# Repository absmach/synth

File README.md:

<div align="center">

### Design circuit boards as code.

Turn text-based circuit designs into KiCad schematics, PCB layouts, and bills of materials.

[Install](#install) · [Quick Start](#quick-start) · [Features](#features) · [Examples](#examples) · [Documentation](https://absmach.eu/docs/synth/user-guide/quick-start/) · [Contributing](#contributing)

</div>

## Introduction

Synth is an open-source compiler for electronic circuit boards. Describe components, connections, and board constraints in **SynthSpec**, a text-based design language; Synth checks the design and generates KiCad schematics, PCB layouts, and a bill of materials. Your `.synth` files hold the design intent, so you can edit them in your usual editor and review changes in Git. Engineers drive it from the command line, and AI agents drive the same compiler through its **Model Context Protocol (MCP)** server.

```synth
board "env_logger" {
    layers 2
    manufacturer "jlcpcb"

    group "USB-C INPUT / 3V3 LDO" color "#c2410c" {
      component J1: connector "usb_c_receptacle"
      component U1: regulator "ams1117_3v3" value "AMS1117-3.3"
      component C2: capacitor "c_generic_0805" value "22uF"
    }

    connect J1.vbus -> U1.vin
    connect J1.gnd  -> U1.gnd
    connect U1.vin  -> C2.p1
}
```

_An excerpt from the [environmental logger](examples/env_logger/env_logger.synth); the full design adds the MCU, sensor, CC pull-downs, and decoupling that the checks require._

<div align="center">

_An agent designing a two-layer NE555 LED blinker through the MCP server: searching the registry, authoring a missing part, setting placement overrides, and validating the board._

</div>

## Install

### Prebuilt binary

Every [release](https://github.com/absmach/synth/releases) ships a `synth` binary for five platforms, each with a SHA-256 checksum beside it.

| Platform       | Asset                     |
| -------------- | ------------------------- |
| Linux x86-64   | `synth-linux-amd64`       |
| Linux arm64    | `synth-linux-arm64`       |
| macOS arm64    | `synth-darwin-arm64`      |
| macOS x86-64   | `synth-darwin-amd64`      |
| Windows x86-64 | `synth-windows-amd64.exe` |

```bash
base="https://github.com/absmach/synth/releases/latest/download"
asset="synth-linux-amd64"          # pick your platform from the table above

curl -LO "$base/$asset"
curl -LO "$base/$asset.sha256"
sha256sum -c "$asset.sha256"       # macOS: shasum -a 256 -c "$asset.sha256"

sudo install -m 755 "$asset" /usr/local/bin/synth
synth --version
```

Verify the checksum before running the binary. On Windows, check it with `certutil -hashfile synth-windows-amd64.exe SHA256` and compare against the `.sha256` file.

The Linux binaries are built against glibc 2.35, so they run on Debian Bookworm, Ubuntu 22.04, and newer.

> [!NOTE]
> The component registry and example designs ship inside the repository and track `main`, which has moved ahead of the latest release. Pair a prebuilt binary with its own tag (`git checkout v0.1.1`, where the example paths differ from those below), or install from source to follow the Quick Start as written.

### Cargo

Synth is not on crates.io, so install it from Git. Requires Rust 1.85 or newer.

```bash
# Latest release
cargo install --git https://github.com/absmach/synth --tag v0.1.1 --locked synth-cli

# Current main
cargo install --git https://github.com/absmach/synth --locked synth-cli
```

> [!WARNING]
> Do not run `cargo install synth-cli`. The `synth-cli` crate on crates.io is an unrelated project — a WebAssembly-to-ARM compiler — not this one.

### From source

```bash
git clone https://github.com/absmach/synth.git
cd synth
cargo build -p synth-cli --release
./target/release/synth --help
```

The repository pins its toolchain in `rust-toolchain.toml`, so rustup fetches the right version automatically.

## Quick Start

Validate the minimal example and export a KiCad project. The example designs come from a checkout, so clone the repository (or `cd` into it) first:

```bash
synth validate fixtures/designs/hello.synth
synth export-kicad fixtures/designs/hello.synth --out output/hello
```

The minimal example declares an empty two-layer board. Use the [example designs](#examples) to explore circuits with components and connections.

For machine-readable diagnostics:

```bash
synth validate examples/env_logger/env_logger.synth --format json
```

Open exported projects in KiCad. Optional Gerber, drill, and STEP exports require `kicad-cli`; see the [KiCad workflow guide](docs/kicad-workflows.md) for export and review details.

For CI and release gates, `synth check DESIGN.synth --json` is the deterministic, model-free gate for validation and DRC. A check that could not run is reported as `unknown` and blocks just as a failure does — see [release checks](docs/release-checks.md).

### Logging

Progress, retries, and degraded-check notices go to stderr as structured log events; stdout carries only the command's own output (JSON, reports, listings), so a pipeline can parse it without stripping prefixes. The default level is info. `-v` raises it to debug, `-vv` to trace, and `-q` shows errors only. `SYNTH_LOG` overrides both when one stage needs more detail:

```bash
synth -v export-kicad board.synth --out output/board
SYNTH_LOG=synth_router=debug,synth=info synth route board.synth
```

### Agent Integration

Start the MCP server over standard input and output:

```bash
synth mcp --stdio
```

Agents can retrieve the SynthSpec language reference, search the registry, validate designs, apply fixes, and invoke compiler stages. See the [MCP guide](crates/synth-mcp/README.md) for transports and tool details.

## How It Works

```mermaid
flowchart LR
    source["SynthSpec source"] --> compiler["Parse & resolve"]
    compiler --> checks["Validate"]
    checks --> layout["Place & route"]
    layout --> export["KiCad project & BOM"]
    checks --> feedback["Diagnostics & fixes"]
    feedback --> source
```

Synth resolves parts from a component registry and lowers the source into a typed board representation. Compiler stages use that shared representation for electrical checks, layout, routing, and export. A local browser viewer displays the schematic and diagnostics as you edit.

## Features

| Area               | Capabilities                                                                                                                                    |
| ------------------ | ----------------------------------------------------------------------------------------------------------------------------------------------- |
| Design language    | SynthSpec parser, typed board IR, components, connections, differential pairs, keepouts, and placement hints                                    |
| Validation         | Electrical-rule checks, design-rule checks, structured diagnostics with source locations and suggested fixes, and SMT-backed quantitative fixes |
| Layout and routing | Deterministic schematic layout, component placement, and multilayer routing, so generated artifacts are reproducible                            |
| KiCad integration  | Project, schematic, PCB, and BOM export; optional fabrication outputs through `kicad-cli`                                                       |
| Component registry | Versioned parts, project and user overlays, search, import, and authoring tools                                                                 |
| Developer tools    | CLI, JSON diagnostics, and an MCP server exposing validation, registry search, placement, routing, and export                                   |

## Examples

| Design                                                                                             | What it demonstrates                                                          |
| -------------------------------------------------------------------------------------------------- | ----------------------------------------------------------------------------- |
| [Hello](fixtures/designs/hello.synth)                                                              | The smallest board declaration                                                |
| [Resistor divider](examples/divider/divider.synth)                                                 | A DC operating-point simulation with `synth sim`                              |
| [RC filter](examples/rc_filter/rc_filter.synth)                                                    | An AC sweep measuring the -3 dB corner with `synth sim`                       |
| [LED current](examples/led/led.synth)                                                              | A branch-current measure checked against a limit with `synth sim`             |
| [Environmental logger](examples/env_logger/env_logger.synth)                                       | USB-C power, a regulator, an MCU, an environmental sensor, and a debug header |
| [Sensor logger](examples/sensor_logger/sensor_logger.synth)                                        | A larger design with dual I²C sensors, SPI flash, and status LEDs             |
| [Placement and differential pairs](examples/placement_and_diff_pair/placement_and_diff_pair.synth) | Placement hints, differential-pair constraints, and keepout regions           |
| [RP2350 development board](examples/rp2350/)                                                       | Clean-netlist FreeRouting, zone refill, and compact outlines                  |

Additional language and validation cases live in [fixtures](fixtures/designs/README.md). Part definitions live in the [component registry](registry/README.md).

_Pre-generated compact RP2350 routed review artifact; open the [KiCad board](examples/rp2350/rp2350_devboard_freerouting_clean.kicad_pcb)
for an interactive review._

## Documentation

- [Release checks](docs/release-checks.md) — the `synth check` gate, tri-state native stages, and export overrides.
- [KiCad workflows](docs/kicad-workflows.md) — exported projects, validation, BOMs, and fabrication outputs.
- [SPICE simulation](docs/spice-sim.md) — `synth sim` testbenches, analyses, measures and ngspice setup.
- [Schematic procedures](docs/schematic-procedures.md) — schematic generation and review.
- [Diagnostic reference](docs/diagnostics/README.md) — diagnostic codes and repair guidance.
- [Diagnostic protocol](docs/protocol-v1.0.md) — the machine-readable diagnostic format.
- [Component registry](registry/README.md) — part definitions and registry structure.
- [MCP server](crates/synth-mcp/README.md) — agent tools and integration.

## Contributing

Contributions to the compiler, component registry, examples, and documentation are welcome. Use [issues](https://github.com/absmach/synth/issues) to report bugs or discuss a change, and submit a pull request with a focused description and relevant validation.

Before submitting code, run the workspace checks:

```bash
make verify
```

This checks formatting, compilation, Clippy lints, the workspace tests, and registry tests. Run `make help` to see individual development commands.

## License

Synth is licensed under the [Apache License 2.0](LICENSE).

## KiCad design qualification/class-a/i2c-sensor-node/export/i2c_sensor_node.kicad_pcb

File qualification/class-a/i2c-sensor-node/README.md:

# I²C sensor node

A field sensor node: JST-fed 5 V into a 3V3 LDO, an STM32G030 reading two I²C
devices — an environmental sensor and a config EEPROM — with a 4-pin JST
break-out for the host UART. One bus, one set of pull-ups.

Design rationale is in the source comments next to the circuits it explains;
this file is the specification.

## Board

| | |
| --- | --- |
| Size | 78.85 × 43.50 mm |
| Layers | 2 |
| Process | JLCPCB standard (0.127 mm track/clearance, 0.3 mm drill, 0.13 mm ring) |
| Components | 19 |
| Nets | 10 |
| Source | `i2c_sensor_node.synth` |

## Supply

| Rail | Source | Protection |
| --- | --- | --- |
| 5 V in | J1, 2-pin JST PH | F1 500 mA polyfuse, then D1 SS14 series Schottky |
| 3V3 | U1 AMS1117-3.3 | 10 µF in, 1 µF out |

Polyfuse before the Schottky: resettable over-current first, then
reverse-polarity, so a reversed supply meets a blocking diode and a fault
current meets a part that resets rather than one that burns.

## Connectors

| Ref | Part | Carries |
| --- | --- | --- |
| J1 | 2-pin JST PH | 5 V, GND |
| J2 | 4-pin JST PH | host UART, with D2 and D3 clamping both lines |

## I²C bus

One bus, 4.7 kΩ pull-ups on both lines, two devices: a BME680 environmental
sensor and a 24LC256 EEPROM. Each carries its own 100 nF, hinted to sit beside
the part rather than wherever the placer would otherwise put it.

## Measured

One local run of the export and the external router.

| | |
| --- | --- |
| Nets closed | **10 of 10** |
| Open | **0** |
| Routed copper | 408.9 mm over 155 segments and 15 vias |
| Tracks below the 0.127 mm floor | **0** |
| Vias below the 0.3 mm drill or 0.13 mm ring | **0** |
| `kicad-cli pcb drc` | 9 errors, 0 unconnected items, 10 warnings |

Three consecutive exports produce a byte-identical schematic and BOM.

### DRC detail

| Severity | Finding | Count |
| --- | --- | --- |
| error | clearance | 7 |
| error | via diameter | 2 |
| warning | silkscreen over copper | 6 |
| warning | library footprint mismatch | 3 |
| warning | dangling via | 1 |

Every net on this board closes and no copper is below the fabrication floor.
What remains is seven places where the router worked inside the clearance the
board asked for.

## Limitations

- **Seven clearance violations.** The board routes completely but not to its
  own declared clearance in seven places; each is copper a human would nudge.
- **One via lands inside a pad** and via-in-pad is not declared, so the
  package is refused. On a two-layer board at this pitch that via is avoidable
  by hand.
- Six silkscreen-over-copper warnings are reference designators crossing pads.
  They are cosmetic on a fabricated board and would be fixed in a silkscreen
  pass that Synth does not perform.
- No fabrication artifacts are produced; the package is refused as
  `UNTRUSTED / NOT FOR FABRICATION`.
- No part carries distributor identity, so the BOM is not orderable as it
  stands.

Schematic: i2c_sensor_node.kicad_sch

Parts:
C1, C2, C4: 10uF; C_0805_2012Metric
C3: 47uF; CP_EIA-3528-21_Kemet-B
C5, C6, C8, C10, C11, C12: 100nF; C_0603_1608Metric
C7: 4.7uF; C_0603_1608Metric
D1, D14: 1N5819; D_SOD-123; MPN 1N5819HW-7-F; LCSC C82544
D4: PTVS6V0S1UR; Nexperia_CFP3_SOD-123W; MPN PTVS6V0S1UR
D7, D8, D9, D10, D11, D12, D13, D19, D20, D21, D22, D23, D24: 3.3V zener; D_SOD-123
D15: GREEN; LED_0603_1608Metric; MPN LTST-C190KGKT
F1: 0.5A hold; Fuse_1812_4532Metric
H2, H3: (no value); MountingHole_2.5mm
J1: JST S2B-XH-A-1; JST_XH_S2B-XH-A-1_1x02_P2.50mm_Horizontal
J3: JST S4B-PH-K-S; JST_PH_S4B-PH-K_1x04_P2.00mm_Horizontal
J4: SWD; PinHeader_1x05_P2.54mm_Vertical
J5: GPIO; PinHeader_1x12_P2.54mm_Vertical
R3: 10k; R_0603_1608Metric
R9, R10: 4.7k; R_0603_1608Metric
R11, R15, R16, R17, R18, R19, R20, R21, R22: 330; R_0603_1608Metric
R12: 1k; R_0603_1608Metric
R13, R14: 100; R_0603_1608Metric
R23: 100; R_0805_2012Metric
R24: 680; R_0603_1608Metric
SW1: RESET; SW_SPST_PTS645Sx43SMTR92
U1: AMS1117-3.3; SOT-223-3_TabPin2; MPN AMS1117-3.3; LCSC C6186
U2: STM32G030F6P6; TSSOP-20_4.4x6.5mm_P0.65mm; MPN STM32G030F6P6
U3: BME680; Bosch_LGA-8_3x3mm_P0.8mm_ClockwisePinNumbering; MPN BME680
U5: 24LC256-I/SN; SOIC-8_3.9x4.9mm_P1.27mm; MPN 24LC256-I/SN; LCSC C411625

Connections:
3V3_REF: J3.4, J4.1, J5.1, R23.2
+3V3: C3.1, C4.1, C5.1, C6.1, C7.1, C10.1, C11.1, C12.1, D14.2 (A), R3.1, R9.1, R10.1, R24.1, U1.2 (VO), U2.4 (VDD), U3.2 (CSB), U3.6 (VDDIO), U3.8 (VDD), U5.8 (VCC)
+5V_PROT: C1.1, C2.1, D1.1 (K), D4.1 (K), U1.3 (VI)
GND: C1.2, C2.2, C3.2, C4.2, C5.2, C6.2, C7.2, C8.2, C10.2, C11.2, C12.2, D4.2 (A), D7.2 (A), D8.2 (A), D9.2 (A), D10.2 (A), D11.2 (A), D12.2 (A), D13.2 (A), D15.1 (K), D19.2 (A), D20.2 (A), D21.2 (A), D22.2 (A), D23.2 (A), D24.2 (A), J1.2, J3.1, J4.4, J5.2, J5.6, J5.10, SW1.2, U1.1 (GND), U2.5 (VSS), U3.1 (GND), U3.5 (SDO), U3.7 (GND), U5.1 (A0), U5.2 (A1), U5.3 (A2), U5.4 (GND), U5.7 (WP)
GPIO_PA0: J5.3, R15.2
GPIO_PA0_MCU: D10.1 (K), R15.1, U2.7 (PA0)
GPIO_PA1: J5.4, R16.2
GPIO_PA1_MCU: D20.1 (K), R16.1, U2.8 (PA1)
GPIO_PA4: J5.5, R17.2
GPIO_PA4_MCU: D11.1 (K), R17.1, U2.11 (PA4)
GPIO_PA5: J5.7, R18.2
GPIO_PA5_MCU: D21.1 (K), R18.1, U2.12 (PA5)
GPIO_PA6: J5.8, R19.2
GPIO_PA6_MCU: D12.1 (K), R19.1, U2.13 (PA6)
GPIO_PA7: J5.9, R20.2
GPIO_PA7_MCU: D22.1 (K), R20.1, U2.14 (PA7)
GPIO_PB0: J5.11, R21.2
GPIO_PB0_MCU: D13.1 (K), R21.1, U2.15 (PA8/PB0/PB1/PB2)
GPIO_PB9: J5.12, R22.2
GPIO_PB9_MCU: D23.1 (K), R22.1, U2.2 (PB9/PC14)
I2C_SCL: R10.2, U2.20 (PB3/PB4/PB5/PB6), U3.4 (SCK), U5.6 (SCL)
I2C_SDA: R9.2, U2.1 (PB7/PB8), U3.3 (SDI), U5.5 (SDA)
LED_PWR: D15.2 (A), R24.2
NRST: C8.1, D19.1 (K), J4.5, R3.2, SW1.1, U2.6 (NRST)
REF_D: D14.1 (K), R23.1
SWCLK: D9.1 (K), J4.3, R14.2
SWCLK_MCU: R14.1, U2.19 (PA14/PA15)
SWDIO: D8.1 (K), J4.2, R13.2
SWDIO_MCU: R13.1, U2.18 (PA13)
U2_RX: D24.1 (K), R12.1, U2.10 (PA3)
U2_TX: D7.1 (K), R11.1, U2.9 (PA2)
UART_RX: J3.3, R12.2
UART_TX: J3.2, R11.2
VIN_5V_FUSED: D1.2 (A), F1.2
VIN_5V_RAW: F1.1, J1.1

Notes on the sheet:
5V INPUT: FUSE THEN DIODE
3V3 REGULATOR
STM32G030 MCU
I2C SENSING
UART BREAKOUT
GPIO HEADER
MOUNTING
J1 pin 1 = +5 V, pin 2 = GND (JST XHP-2). Fuse first, then the
reverse-polarity diode D1.
D4 clamps transients on +5V_PROT, behind D1 so a reversed supply never
forward-biases it.
AMS1117 tab is VOUT. Load budget 100 mA: P = (5.0 - 3.3) x 0.1 A =
0.17 W, thetaJA 90 C/W gives a 15 C rise (125 C limit).
LED (VF 1.9 to 2.4 V): 1.3 to 2.1 mA through 680 R. C3 is 47 uF
tantalum (22 uF required).
J4: 1 = 3V3_REF, 2 = SWDIO, 3 = SWCLK, 4 = GND, 5 = NRST. PA14 is
SWCLK and BOOT0.
D8, D9, D19 are 3.3 V zeners; a 5 V fault through 100 R is (5 - 3.3) /
100 = 17 mA, 56 mW.
BME680 SDO low = 0x76, CSB high = I2C. 24LC256 A2:A0 low = 0x50. No
collision.
One pull-up pair, 4.7k each, for the whole bus.
J3: 1 GND, 2 UART_TX, 3 UART_RX, 4 3V3_REF (3 mA max). Host logic 3.3
V to 5 V.
D7, D24 are 3.3 V zeners behind 330 R and 1 k: a 5 V fault is 5.2 mA
(17 mW) and 1.7 mA (5.6 mW).
J5: 1 3V3_REF, 2 GND, 3 PA0, 4 PA1, 5 PA4, 6 GND, 7 PA5, 8 PA6, 9 PA7,
10 GND, 11 PB0, 12 PB9.
D10..D13, D20..D23: one 3.3 V zener per line behind 330 R; a 5 V fault
is 5.2 mA, 17 mW. 3V3_REF is +3V3 through D14 and 100 R, 3 mA max.
H2, H3: two M2.5 non-plated mounting holes at opposite (diagonal)
corners.

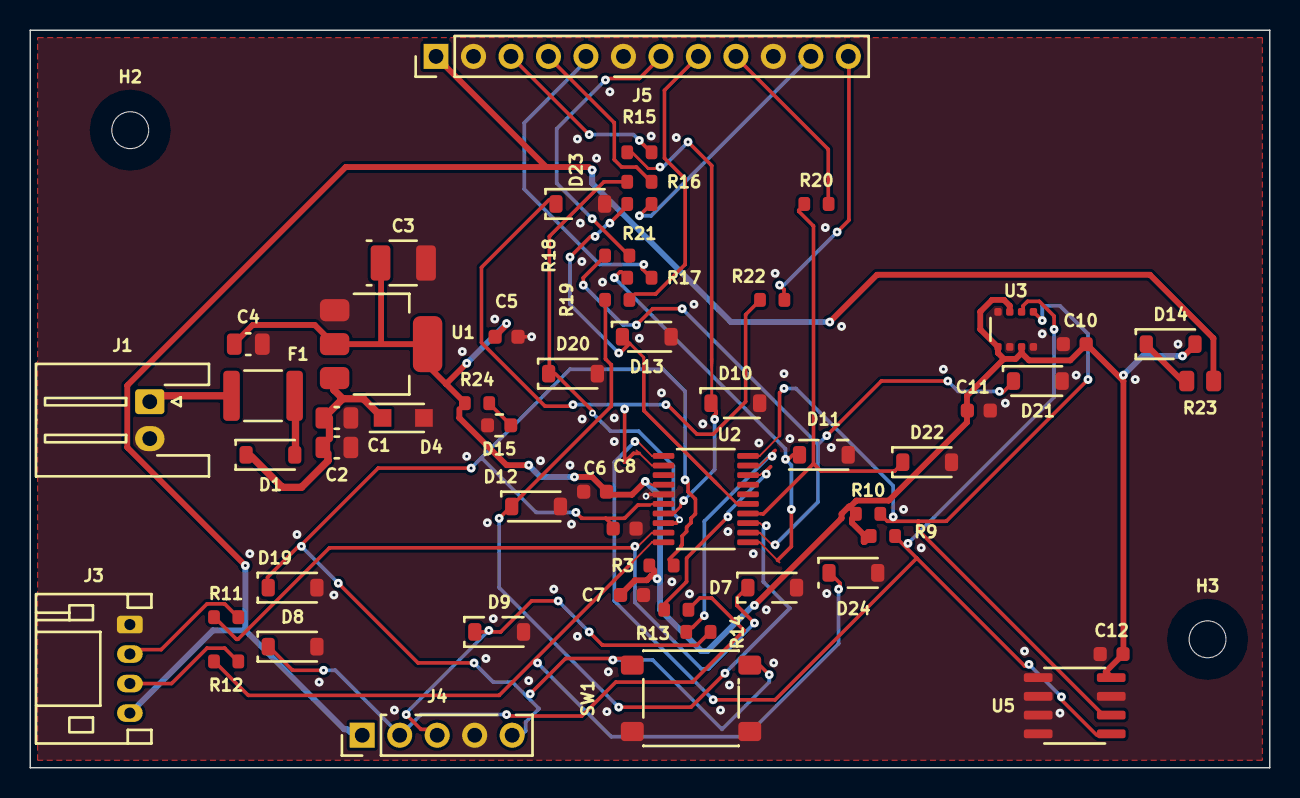
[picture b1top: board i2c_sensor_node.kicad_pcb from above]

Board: 2 copper layers, 84.0 x 50.0 mm, 57 parts (0 on the bottom side), 35 nets.

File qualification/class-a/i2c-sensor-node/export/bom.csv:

refdes,value,kind,description,kicad_symbol,kicad_footprint,lcsc_pn,mpn
C1,10uF,capacitor,"Generic 0805 MLCC, X7R/X5R, any value",Device:C,Capacitor_SMD:C_0805_2012Metric,,
C10,100nF,capacitor,"Generic 0603 MLCC, X7R/X5R, any value",Device:C,Capacitor_SMD:C_0603_1608Metric,,
C11,100nF,capacitor,"Generic 0603 MLCC, X7R/X5R, any value",Device:C,Capacitor_SMD:C_0603_1608Metric,,
C12,100nF,capacitor,"Generic 0603 MLCC, X7R/X5R, any value",Device:C,Capacitor_SMD:C_0603_1608Metric,,
C2,10uF,capacitor,"Generic 0805 MLCC, X7R/X5R, any value",Device:C,Capacitor_SMD:C_0805_2012Metric,,
C3,47uF,capacitor,"47µF 16V tantalum capacitor, polarised, 3528 case",Device:C_Polarized,Capacitor_Tantalum_SMD:CP_EIA-3528-21_Kemet-B,,
C4,10uF,capacitor,"Generic 0805 MLCC, X7R/X5R, any value",Device:C,Capacitor_SMD:C_0805_2012Metric,,
C5,100nF,capacitor,"Generic 0603 MLCC, X7R/X5R, any value",Device:C,Capacitor_SMD:C_0603_1608Metric,,
C6,100nF,capacitor,"Generic 0603 MLCC, X7R/X5R, any value",Device:C,Capacitor_SMD:C_0603_1608Metric,,
C7,4.7uF,capacitor,"Generic 0603 MLCC, X7R/X5R, any value",Device:C,Capacitor_SMD:C_0603_1608Metric,,
C8,100nF,capacitor,"Generic 0603 MLCC, X7R/X5R, any value",Device:C,Capacitor_SMD:C_0603_1608Metric,,
D1,1N5819,diode,"Diodes Inc. 1N5819HW-7-F, 40 V 1 A Schottky diode, SOD-123, low forward voltage",Device:D_Schottky,Diode_SMD:D_SOD-123,C82544,1N5819HW-7-F
D10,3.3V zener,diode,"3.3V Zener diode, SOD-123",Device:D_Zener,Diode_SMD:D_SOD-123,,
D11,3.3V zener,diode,"3.3V Zener diode, SOD-123",Device:D_Zener,Diode_SMD:D_SOD-123,,
D12,3.3V zener,diode,"3.3V Zener diode, SOD-123",Device:D_Zener,Diode_SMD:D_SOD-123,,
D13,3.3V zener,diode,"3.3V Zener diode, SOD-123",Device:D_Zener,Diode_SMD:D_SOD-123,,
D14,1N5819,diode,"Diodes Inc. 1N5819HW-7-F, 40 V 1 A Schottky diode, SOD-123, low forward voltage",Device:D_Schottky,Diode_SMD:D_SOD-123,C82544,1N5819HW-7-F
D15,GREEN,diode,"Lite-On LTST-C190KGKT green AlInGaP LED, 0603, Vf 1.9 to 2.4V at 20mA",Device:LED,LED_SMD:LED_0603_1608Metric,,LTST-C190KGKT
D19,3.3V zener,diode,"3.3V Zener diode, SOD-123",Device:D_Zener,Diode_SMD:D_SOD-123,,
D20,3.3V zener,diode,"3.3V Zener diode, SOD-123",Device:D_Zener,Diode_SMD:D_SOD-123,,
D21,3.3V zener,diode,"3.3V Zener diode, SOD-123",Device:D_Zener,Diode_SMD:D_SOD-123,,
D22,3.3V zener,diode,"3.3V Zener diode, SOD-123",Device:D_Zener,Diode_SMD:D_SOD-123,,
D23,3.3V zener,diode,"3.3V Zener diode, SOD-123",Device:D_Zener,Diode_SMD:D_SOD-123,,
D24,3.3V zener,diode,"3.3V Zener diode, SOD-123",Device:D_Zener,Diode_SMD:D_SOD-123,,
D4,PTVS6V0S1UR,diode,"Nexperia PTVS6V0S1UR 400 W unidirectional TVS, 6.0 V standoff, SOD123W, for VBUS and CC",Device:D_Zener,Diode_SMD:Nexperia_CFP3_SOD-123W,,PTVS6V0S1UR
D7,3.3V zener,diode,"3.3V Zener diode, SOD-123",Device:D_Zener,Diode_SMD:D_SOD-123,,
D8,3.3V zener,diode,"3.3V Zener diode, SOD-123",Device:D_Zener,Diode_SMD:D_SOD-123,,
D9,3.3V zener,diode,"3.3V Zener diode, SOD-123",Device:D_Zener,Diode_SMD:D_SOD-123,,
F1,0.5A hold,fuse,"Resettable polyfuse (PPTC), 0.5 A hold, 2-pin, 1812. Generic: MPN needs sourcing.",Device:Polyfuse,Fuse:Fuse_1812_4532Metric,,
H2,(no value),mounting_hole,M2.5 non-plated mounting hole (NPTH) for a board corner,Mechanical:MountingHole,MountingHole:MountingHole_2.5mm,,
H3,(no value),mounting_hole,M2.5 non-plated mounting hole (NPTH) for a board corner,Mechanical:MountingHole,MountingHole:MountingHole_2.5mm,,
J1,JST S2B-XH-A-1,connector,"JST XH-series 2-pin wire-to-board connector, 2.0mm pitch",Connector_Generic:Conn_01x02,Connector_JST:JST_XH_S2B-XH-A-1_1x02_P2.50mm_Horizontal,,
J3,JST S4B-PH-K-S,connector,"JST PH-series 4-pin wire-to-board connector, 2.0mm pitch",Connector_Generic:Conn_01x04,Connector_JST:JST_PH_S4B-PH-K_1x04_P2.00mm_Horizontal,,
J4,SWD,connector,"1x5 through-hole pin header, 2.54 mm pitch (SWD); datasheet_url is the product page of the Harwin M20 series, no manufacturer PDF link was verifiable",Connector_Generic:Conn_01x05,Connector_PinHeader_2.54mm:PinHeader_1x05_P2.54mm_Vertical,,
J5,GPIO,connector,"1x12 through-hole pin header, 2.54 mm pitch (GPIO); datasheet_url is the product page of the Harwin M20 series, no manufacturer PDF link was verifiable",Connector_Generic:Conn_01x12,Connector_PinHeader_2.54mm:PinHeader_1x12_P2.54mm_Vertical,,
R10,4.7k,resistor,"Generic 0603 thick-film resistor, any value",Device:R_US,Resistor_SMD:R_0603_1608Metric,,
R11,330,resistor,"Generic 0603 thick-film resistor, any value",Device:R_US,Resistor_SMD:R_0603_1608Metric,,
R12,1k,resistor,"Generic 0603 thick-film resistor, any value",Device:R_US,Resistor_SMD:R_0603_1608Metric,,
R13,100,resistor,"Generic 0603 thick-film resistor, any value",Device:R_US,Resistor_SMD:R_0603_1608Metric,,
R14,100,resistor,"Generic 0603 thick-film resistor, any value",Device:R_US,Resistor_SMD:R_0603_1608Metric,,
R15,330,resistor,"Generic 0603 thick-film resistor, any value",Device:R_US,Resistor_SMD:R_0603_1608Metric,,
R16,330,resistor,"Generic 0603 thick-film resistor, any value",Device:R_US,Resistor_SMD:R_0603_1608Metric,,
R17,330,resistor,"Generic 0603 thick-film resistor, any value",Device:R_US,Resistor_SMD:R_0603_1608Metric,,
R18,330,resistor,"Generic 0603 thick-film resistor, any value",Device:R_US,Resistor_SMD:R_0603_1608Metric,,
R19,330,resistor,"Generic 0603 thick-film resistor, any value",Device:R_US,Resistor_SMD:R_0603_1608Metric,,
R20,330,resistor,"Generic 0603 thick-film resistor, any value",Device:R_US,Resistor_SMD:R_0603_1608Metric,,
R21,330,resistor,"Generic 0603 thick-film resistor, any value",Device:R_US,Resistor_SMD:R_0603_1608Metric,,
R22,330,resistor,"Generic 0603 thick-film resistor, any value",Device:R_US,Resistor_SMD:R_0603_1608Metric,,
R23,100,resistor,"Generic 0805 thick-film resistor, any value",Device:R_US,Resistor_SMD:R_0805_2012Metric,,
R24,680,resistor,"Generic 0603 thick-film resistor, any value",Device:R_US,Resistor_SMD:R_0603_1608Metric,,
R3,10k,resistor,"Generic 0603 thick-film resistor, any value",Device:R_US,Resistor_SMD:R_0603_1608Metric,,
R9,4.7k,resistor,"Generic 0603 thick-film resistor, any value",Device:R_US,Resistor_SMD:R_0603_1608Metric,,
SW1,RESET,switch,Generic SPST tactile button,Switch:SW_Push,Button_Switch_SMD:SW_SPST_PTS645Sx43SMTR92,,
U1,AMS1117-3.3,regulator,"AMS1117-3.3 fixed 3.3V LDO regulator, SOT-223 — common JLC stock",Regulator_Linear:AMS1117-3.3,Package_TO_SOT_SMD:SOT-223-3_TabPin2,C6186,AMS1117-3.3
U2,STM32G030F6P6,mcu,"STMicro STM32G030F6P6 Cortex-M0+ 64 MHz, 32 KB flash, 8 KB RAM, TSSOP-20. Pin map checked against KiCad MCU_ST_STM32G0:STM32G030F6Px",MCU_ST_STM32G0:STM32G030F6Px,Package_SO:TSSOP-20_4.4x6.5mm_P0.65mm,,STM32G030F6P6
U3,BME680,sensor,"Bosch BME680 T/RH/P/gas sensor, 3.0x3.0 mm 8-pin LGA, I2C/SPI. Pins checked against KiCad Sensor:BME680; footprint is the 3x3 mm 0.8 mm pitch one whose KiCad description cites the BME680 datasheet",Sensor:BME680,Package_LGA:Bosch_LGA-8_3x3mm_P0.8mm_ClockwisePinNumbering,,BME680
U5,24LC256-I/SN,memory,"Microchip 24LC256-I/SN 256 Kbit I2C EEPROM, SOIC-8. Pin map checked against KiCad Memory_EEPROM:24LC256",Memory_EEPROM:24LC256,Package_SO:SOIC-8_3.9x4.9mm_P1.27mm,C411625,24LC256-I/SN

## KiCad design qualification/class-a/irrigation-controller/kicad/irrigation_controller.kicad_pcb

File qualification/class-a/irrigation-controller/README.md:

# Irrigation controller (Class A, case 1)

A two-zone irrigation controller powered from 12 V DC: an input fuse, a TVS and an ideal-diode reverse-polarity stage, an MP2307 buck to 3.3 V, an STM32G030 microcontroller, two low-side solenoid drivers, two switched resistive soil probes, a flow-pulse input, an I2C header with an ambient light sensor and an EEPROM, an SWD header, and rail decoupling, bleeders, snubbers, indicator LEDs and test points. Two copper layers, JLCPCB process, 79.2 x 70.7 mm, 127 placed items (107 parts and 20 mounting holes and test points). There is no humidity sensor on the board: a breakout attaches to the I2C header at address 0x44.

## The board

| Group | Parts |
|---|---|
| Power input | `J1` JST XH 2-pin supply connector; `F1` Littelfuse 1812L150/16DR resettable fuse (1.5 A hold); `D_TVS` SMAJ13A (13.0 V standoff, 21.5 V clamp at 18.6 A); the ideal-diode stage `U_IDEAL` Texas Instruments LM74700-Q1 (SOT-23-6) driving `Q1` Diodes DMT6007LFG (60 V, 8.5 mOhm maximum at 4.5 V gate drive) with `C_VCAP` and `C_VIN` (100 nF each) at the controller and `C_BULK` (100 uF) on the output; test points `TP_VIN`, `TP_12V` |
| 3.3 V buck | `U1` MPS MP2307DN, input capacitors `C_IN1` and `C_IN2` (10 uF), inductor `L1` Bourns SRN6045TA-100M (10 uH), output capacitors `C_OUT1` and `C_OUT2` (22 uF), feedback divider `R_FBT` 26.1 k and `R_FBB` 10 k, compensation `R_COMP` 5.6 k and `C_COMP` 4.7 nF, soft-start `C_SS`, enable divider `R_EN`; test points `TP_3V3`, `TP_GND` |
| MCU | `U2` STMicroelectronics STM32G030K8T6 (LQFP-32), crystal `Y1` JYJE 3TJ480000FYLBC (8 MHz) with `C_X1` and `C_X2` (6.2 pF), supply capacitors `C_VDD1` and `C_VDD2`, reset network `R_NRST`, `C_NRST` and the tactile switch `SW_RESET`, the 5-pin SWD header `J_SWD`; test points `TP_NRST`, `TP_SWDIO`, `TP_SWCLK` |
| Valves 1 and 2 | per valve: a JST XH 2-pin connector (`J_VALVE1`, `J_VALVE2`), a low-side AO3400A N-MOSFET (`Q_V1`, `Q_V2`) with a 100 ohm gate resistor and a 100 k pull-down, a 1N5819HW flyback diode (`D_FLY1`, `D_FLY2`) and an RC snubber (100 ohm, 10 nF) |
| Soil probes 1 and 2 | per probe: a JST PH 3-pin connector (`J_SOIL1`, `J_SOIL2`), a Si2301CDS P-MOSFET that switches the excitation (`Q_E1`, `Q_E2`), the sense divider and a 10 nF filter |
| Flow input | `J_FLOW` JST PH 3-pin, pull-up `R_FPU`, series resistor `R_FS` and a 3.3 V zener `D_FZ` that clamps the pulse input, filter `C_FL` |
| I2C | `J_I2C` JST PH 4-pin, 4.7 k pull-ups `R_SDA` and `R_SCL`, `U4` Broadcom APDS-9301 ambient light sensor, `U5` Microchip 24LC256 EEPROM, each with a 100 nF capacitor |
| Indicators | `D_PWR` and `D_N2` green (Lite-On LTST-C190KGKT), `D_VALVE` and `D_N1` amber (KENTO KT-0603Y), each with a series resistor |
| Rail decoupling and bleeders | the `+3V3` decoupling group (22 parts: capacitors from 100 nF to 10 uF and the bleeders `R_N1` and `R_N2`) and the 12 V decoupling group (7 parts, with the bleeder `R_B1`) |
| Mechanical | four M2.5 mounting holes, one in each corner; test points on the nets listed above |

The qualification verdict, measurements, evidence and sign-off are in [`QUALIFICATION.md`](QUALIFICATION.md); how the board was made is in [`PROVENANCE.md`](PROVENANCE.md). Gerber content hash `a26463bd09`.

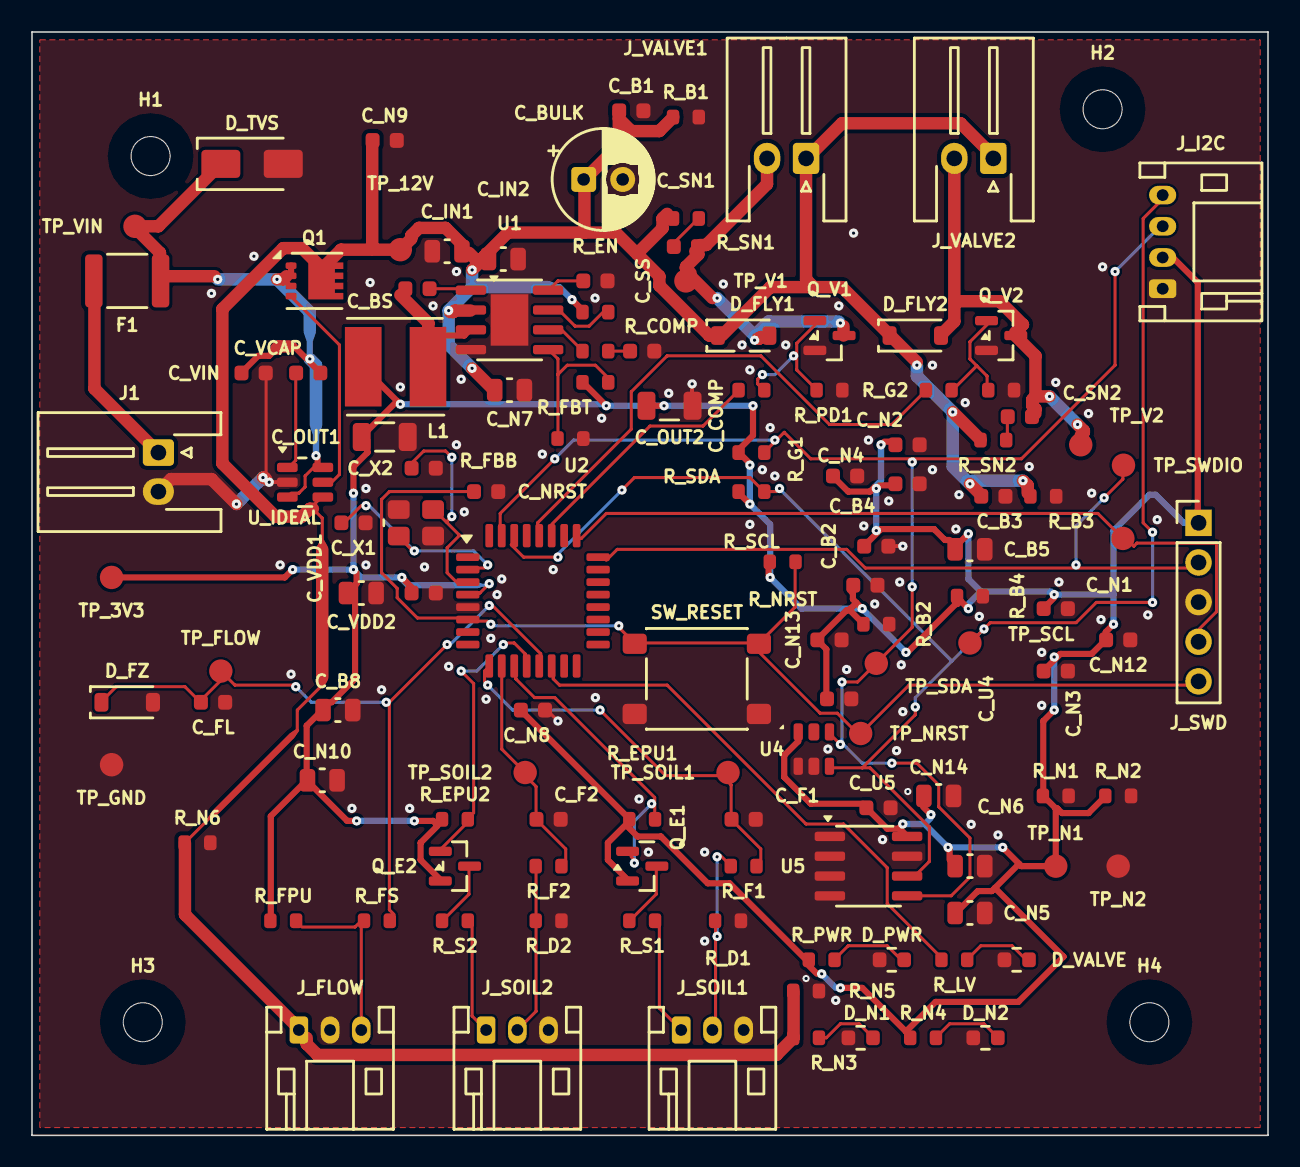
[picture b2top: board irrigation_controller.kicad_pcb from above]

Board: 2 copper layers, 79.2 x 70.7 mm, 127 parts (0 on the bottom side), 46 nets.

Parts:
C_B1, C_B2, C_B3, C_B4: 100nF; C_0603_1608Metric
C_B5, C_B8: 4.7uF; C_0805_2012Metric
C_BS: 10nF; C_0603_1608Metric
C_BULK: 100uF 25V; CP_Radial_D6.3mm_P2.50mm
C_COMP: 4.7nF; C_0603_1608Metric
C_F1, C_F2: 10nF; C_0603_1608Metric
C_FL: 10nF; C_0603_1608Metric
C_IN1, C_IN2: 10uF 25V; C_0805_2012Metric
C_N1, C_N2, C_N3, C_N4, C_N8, C_N9, C_N11, C_N12, C_N13: 100nF; C_0603_1608Metric
C_N5: 10uF; C_0805_2012Metric
C_N6, C_N10, C_N14: 4.7uF; C_0805_2012Metric
C_N7: 10uF 25V; C_0805_2012Metric
C_NRST: 100nF; C_0603_1608Metric
C_OUT1, C_OUT2: 22uF 10V; C_1206_3216Metric
C_SN1, C_SN2: 10nF; C_0603_1608Metric
C_SS: 100nF; C_0603_1608Metric
C_U4, C_U5: 100nF; C_0603_1608Metric
C_VCAP: 100nF; C_0603_1608Metric
C_VDD1: 100nF; C_0603_1608Metric
C_VDD2: 4.7uF; C_0805_2012Metric
C_VIN: 100nF; C_0603_1608Metric
C_X1, C_X2: 6.2pF; C_0603_1608Metric
D_FLY1, D_FLY2: 1N5819HW-7-F; D_SOD-123
D_FZ: (no value); D_SOD-123
D_N1: (no value); LED_0603_1608Metric
D_N2: LTST-C190KGKT; LED_0603_1608Metric
D_PWR: LTST-C190KGKT; LED_0603_1608Metric
D_TVS: SMAJ13A; D_SMA
D_VALVE: (no value); LED_0603_1608Metric
F1: 1812L150/16DR; Fuse_1812_4532Metric
H1, H2, H3, H4: (no value); MountingHole_2.5mm
J1: S2B-XH-A-1(LF)(SN); JST_XH_S2B-XH-A-1_1x02_P2.50mm_Horizontal
J_FLOW: S3B-PH-K-S(LF)(SN); JST_PH_S3B-PH-K_1x03_P2.00mm_Horizontal
J_I2C: S4B-PH-K-S(LF)(SN); JST_PH_S4B-PH-K_1x04_P2.00mm_Horizontal
J_SOIL1, J_SOIL2: S3B-PH-K-S(LF)(SN); JST_PH_S3B-PH-K_1x03_P2.00mm_Horizontal
J_SWD: (no value); PinHeader_1x05_P2.54mm_Vertical
J_VALVE1, J_VALVE2: S2B-XH-A-1(LF)(SN); JST_XH_S2B-XH-A-1_1x02_P2.50mm_Horizontal
L1: SRN6045TA-100M; L_Bourns_SRN6045TA
Q1: DMT6007LFG-7; Diodes_PowerDI3333-8
Q_E1, Q_E2: SI2301CDS-T1-GE3; SOT-23
Q_V1, Q_V2: AO3400A; SOT-23
R_B1, R_B2: 100k; R_0603_1608Metric
R_B3, R_B4: 47k; R_0603_1608Metric
R_COMP: 5.6k; R_0603_1608Metric
R_D1, R_D2: 10k; R_0603_1608Metric
R_EN: 100k; R_0603_1608Metric
R_EPU1, R_EPU2: 100k; R_0603_1608Metric
R_F1, R_F2: 1k; R_0603_1608Metric
R_FBB: 10k; R_0603_1608Metric
R_FBT: 26.1k; R_0603_1608Metric
R_FPU: 10k; R_0603_1608Metric
R_FS: 2.2k; R_0603_1608Metric
R_G1, R_G2: 100; R_0603_1608Metric
R_LV: 680; R_0603_1608Metric
R_N1, R_N5, R_N6: 100k; R_0603_1608Metric
R_N2: 47k; R_0603_1608Metric
R_N3: 2.2k; R_0603_1608Metric
R_N4: 680; R_0603_1608Metric
R_NRST: 10k; R_0603_1608Metric
R_PD1, R_PD2: 100k; R_0603_1608Metric
R_PWR: 680; R_0603_1608Metric
R_S1, R_S2: 1k; R_0603_1608Metric
R_SCL: 4.7k; R_0603_1608Metric
R_SDA: 4.7k; R_0603_1608Metric
R_SN1, R_SN2: 100; R_0603_1608Metric
SW_RESET: PTS645SM43SMTR92 LFS; SW_SPST_PTS645Sx43SMTR92
TP_3V3, TP_12V: (no value); TestPoint_Pad_D1.5mm
TP_FLOW: (no value); TestPoint_Pad_D1.5mm
TP_GND: (no value); TestPoint_Pad_D1.5mm
TP_N1, TP_N2: (no value); TestPoint_Pad_D1.5mm
TP_NRST: (no value); TestPoint_Pad_D1.5mm
TP_SCL: (no value); TestPoint_Pad_D1.5mm
TP_SDA: (no value); TestPoint_Pad_D1.5mm
TP_SOIL1, TP_SOIL2: (no value); TestPoint_Pad_D1.5mm
TP_SWCLK: (no value); TestPoint_Pad_D1.5mm
TP_SWDIO: (no value); TestPoint_Pad_D1.5mm
TP_V1, TP_V2: (no value); TestPoint_Pad_D1.5mm
TP_VIN: (no value); TestPoint_Pad_D1.5mm
U1: MP2307DN-LF-Z; SOIC-8-1EP_3.9x4.9mm_P1.27mm_EP2.41x3.3mm
U2: (no value); LQFP-32_7x7mm_P0.8mm
U4: (no value); Broadcom_APDS-9301
U5: 24LC256-I/SN; SOIC-8_3.9x4.9mm_P1.27mm
U_IDEAL: LM74700QDBVRQ1; SOT-23-6
Y1: 3TJ480000FYLBC; Crystal_SMD_3225-4Pin_3.2x2.5mm

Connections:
+3V3: C_B2.1, C_B4.1, C_B5.1, C_B8.1, C_N1.1, C_N2.1, C_N3.1, C_N4.1, C_N5.1, C_N6.1, C_N8.1, C_N10.1, C_N11.1, C_N12.1, C_N13.1, C_N14.1, C_OUT1.1, C_OUT2.1, C_U4.1, C_U5.1, C_VDD1.1, C_VDD2.1, J_I2C.2, J_SWD.1, L1.2, Q_E1.2, Q_E2.2, R_B2.1, R_B4.1, R_EPU1.1, R_EPU2.1, R_FBT.1, R_FPU.1, R_N1.1, R_N2.1, R_N4.1, R_NRST.1, R_PWR.1, R_SCL.1, R_SDA.1, TP_3V3.1, TP_N1.1, U2.4, U4.1, U5.8
+12V_VALVE: C_B1.1, C_B3.1, C_BULK.1, C_IN1.1, C_IN2.1, C_N7.1, C_N9.1, D_FLY1.1, D_FLY2.1, J_FLOW.1, J_VALVE1.1, J_VALVE2.1, Q1.5, R_B1.1, R_B3.1, R_EN.1, R_N3.1, R_N5.1, R_N6.1, R_SN1.1, R_SN2.1, TP_12V.1, U1.2, U_IDEAL.4
BUCK_BS: C_BS.1, U1.1
BUCK_COMP: R_COMP.1, U1.6
BUCK_COMPC: C_COMP.1, R_COMP.2
BUCK_EN: R_EN.2, U1.7
BUCK_FB: R_FBB.1, R_FBT.2, U1.5
BUCK_SS: C_SS.1, U1.8
BUCK_SW: C_BS.2, L1.1, U1.3
FLOW_IN: J_FLOW.3, R_FPU.2, R_FS.1
FLOW_PULSE: C_FL.1, D_FZ.1, R_FS.2, TP_FLOW.1, U2.13
GND: C_B1.2, C_B2.2, C_B3.2, C_B4.2, C_B5.2, C_B8.2, C_BULK.2, C_COMP.2, C_F1.2, C_F2.2, C_FL.2, C_IN1.2, C_IN2.2, C_N1.2, C_N2.2, C_N3.2, C_N4.2, C_N5.2, C_N6.2, C_N7.2, C_N8.2, C_N9.2, C_N10.2, C_N11.2, C_N12.2, C_N13.2, C_N14.2, C_NRST.2, C_OUT1.2, C_OUT2.2, C_SS.2, C_U4.2, C_U5.2, C_VDD1.2, C_VDD2.2, C_VIN.2, C_X1.2, C_X2.2, D_FZ.2, D_N1.1, D_N2.1, D_PWR.1, D_TVS.2, D_VALVE.1, J1.2, J_FLOW.2, J_I2C.1, J_SOIL1.3, J_SOIL2.3, J_SWD.3, Q_V1.2, Q_V2.2, R_B1.2, R_B2.2, R_B3.2, R_B4.2, R_D1.2, R_D2.2, R_FBB.2, R_N1.2, R_N2.2, R_N5.2, R_N6.2, R_PD1.2, R_PD2.2, SW_RESET.2, TP_GND.1, TP_N2.1, U1.4, U1.9, U2.5, U4.2, U4.3, U5.1, U5.2, U5.3, U5.4, U5.7, U_IDEAL.2, Y1.2, Y1.4
I2C_SCL: J_I2C.4, R_SCL.2, TP_SCL.1, U2.30, U4.4, U5.6
I2C_SDA: J_I2C.3, R_SDA.2, TP_SDA.1, U2.31, U4.5, U5.5
ID_VCAP: C_VCAP.1, U_IDEAL.1
LED_N12_A: D_N1.2, R_N3.2
LED_N33_A: D_N2.2, R_N4.2
LED_PWR_A: D_PWR.2, R_PWR.2
LED_VALVE_A: D_VALVE.2, R_LV.2
LED_VALVE_DRV: R_LV.1, U2.14
NRST: C_NRST.1, J_SWD.5, R_NRST.2, SW_RESET.1, TP_NRST.1, U2.6
OSC_IN: C_X1.1, U2.2, Y1.1
OSC_OUT: C_X2.1, U2.3, Y1.3
Q1_GATE: Q1.4, U_IDEAL.5
SNUB1: C_SN1.1, R_SN1.2
SNUB2: C_SN2.1, R_SN2.2
SOIL1_ADC: C_F1.1, R_F1.2, TP_SOIL1.1, U2.9
SOIL1_EXC: Q_E1.3, R_S1.1
SOIL1_EXC_EN: Q_E1.1, R_EPU1.2, U2.11
SOIL1_PROBE: J_SOIL1.1, R_S1.2
SOIL1_SENSE: J_SOIL1.2, R_D1.1, R_F1.1
SOIL2_ADC: C_F2.1, R_F2.2, TP_SOIL2.1, U2.10
SOIL2_EXC: Q_E2.3, R_S2.1
SOIL2_EXC_EN: Q_E2.1, R_EPU2.2, U2.12
SOIL2_PROBE: J_SOIL2.1, R_S2.2
SOIL2_SENSE: J_SOIL2.2, R_D2.1, R_F2.1
SWCLK: J_SWD.4, TP_SWCLK.1, U2.25
SWDIO: J_SWD.2, TP_SWDIO.1, U2.24
VALVE1_GATE: R_G1.1, U2.27
VALVE1_GATE_Q: Q_V1.1, R_G1.2, R_PD1.1
VALVE1_SW: C_SN1.2, D_FLY1.2, J_VALVE1.2, Q_V1.3, TP_V1.1
VALVE2_GATE: R_G2.1, U2.28
VALVE2_GATE_Q: Q_V2.1, R_G2.2, R_PD2.1
VALVE2_SW: C_SN2.2, D_FLY2.2, J_VALVE2.2, Q_V2.3, TP_V2.1
VIN_12V_RAW: F1.1, J1.1
VIN_FUSED: C_VCAP.2, C_VIN.1, D_TVS.1, F1.2, Q1.1, Q1.2, Q1.3, TP_VIN.1, U_IDEAL.3, U_IDEAL.6

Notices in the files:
README.md:
License: Apache-2.0
